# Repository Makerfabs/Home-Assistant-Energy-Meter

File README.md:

# Makerfabs Home Assistant Energy Meter

## Intruduce

[Product Link]()

[Wiki Link](https://wiki.makerfabs.com/How%20to%20use%20Energy%20Meter%20for%20Home%20Assistant.html)

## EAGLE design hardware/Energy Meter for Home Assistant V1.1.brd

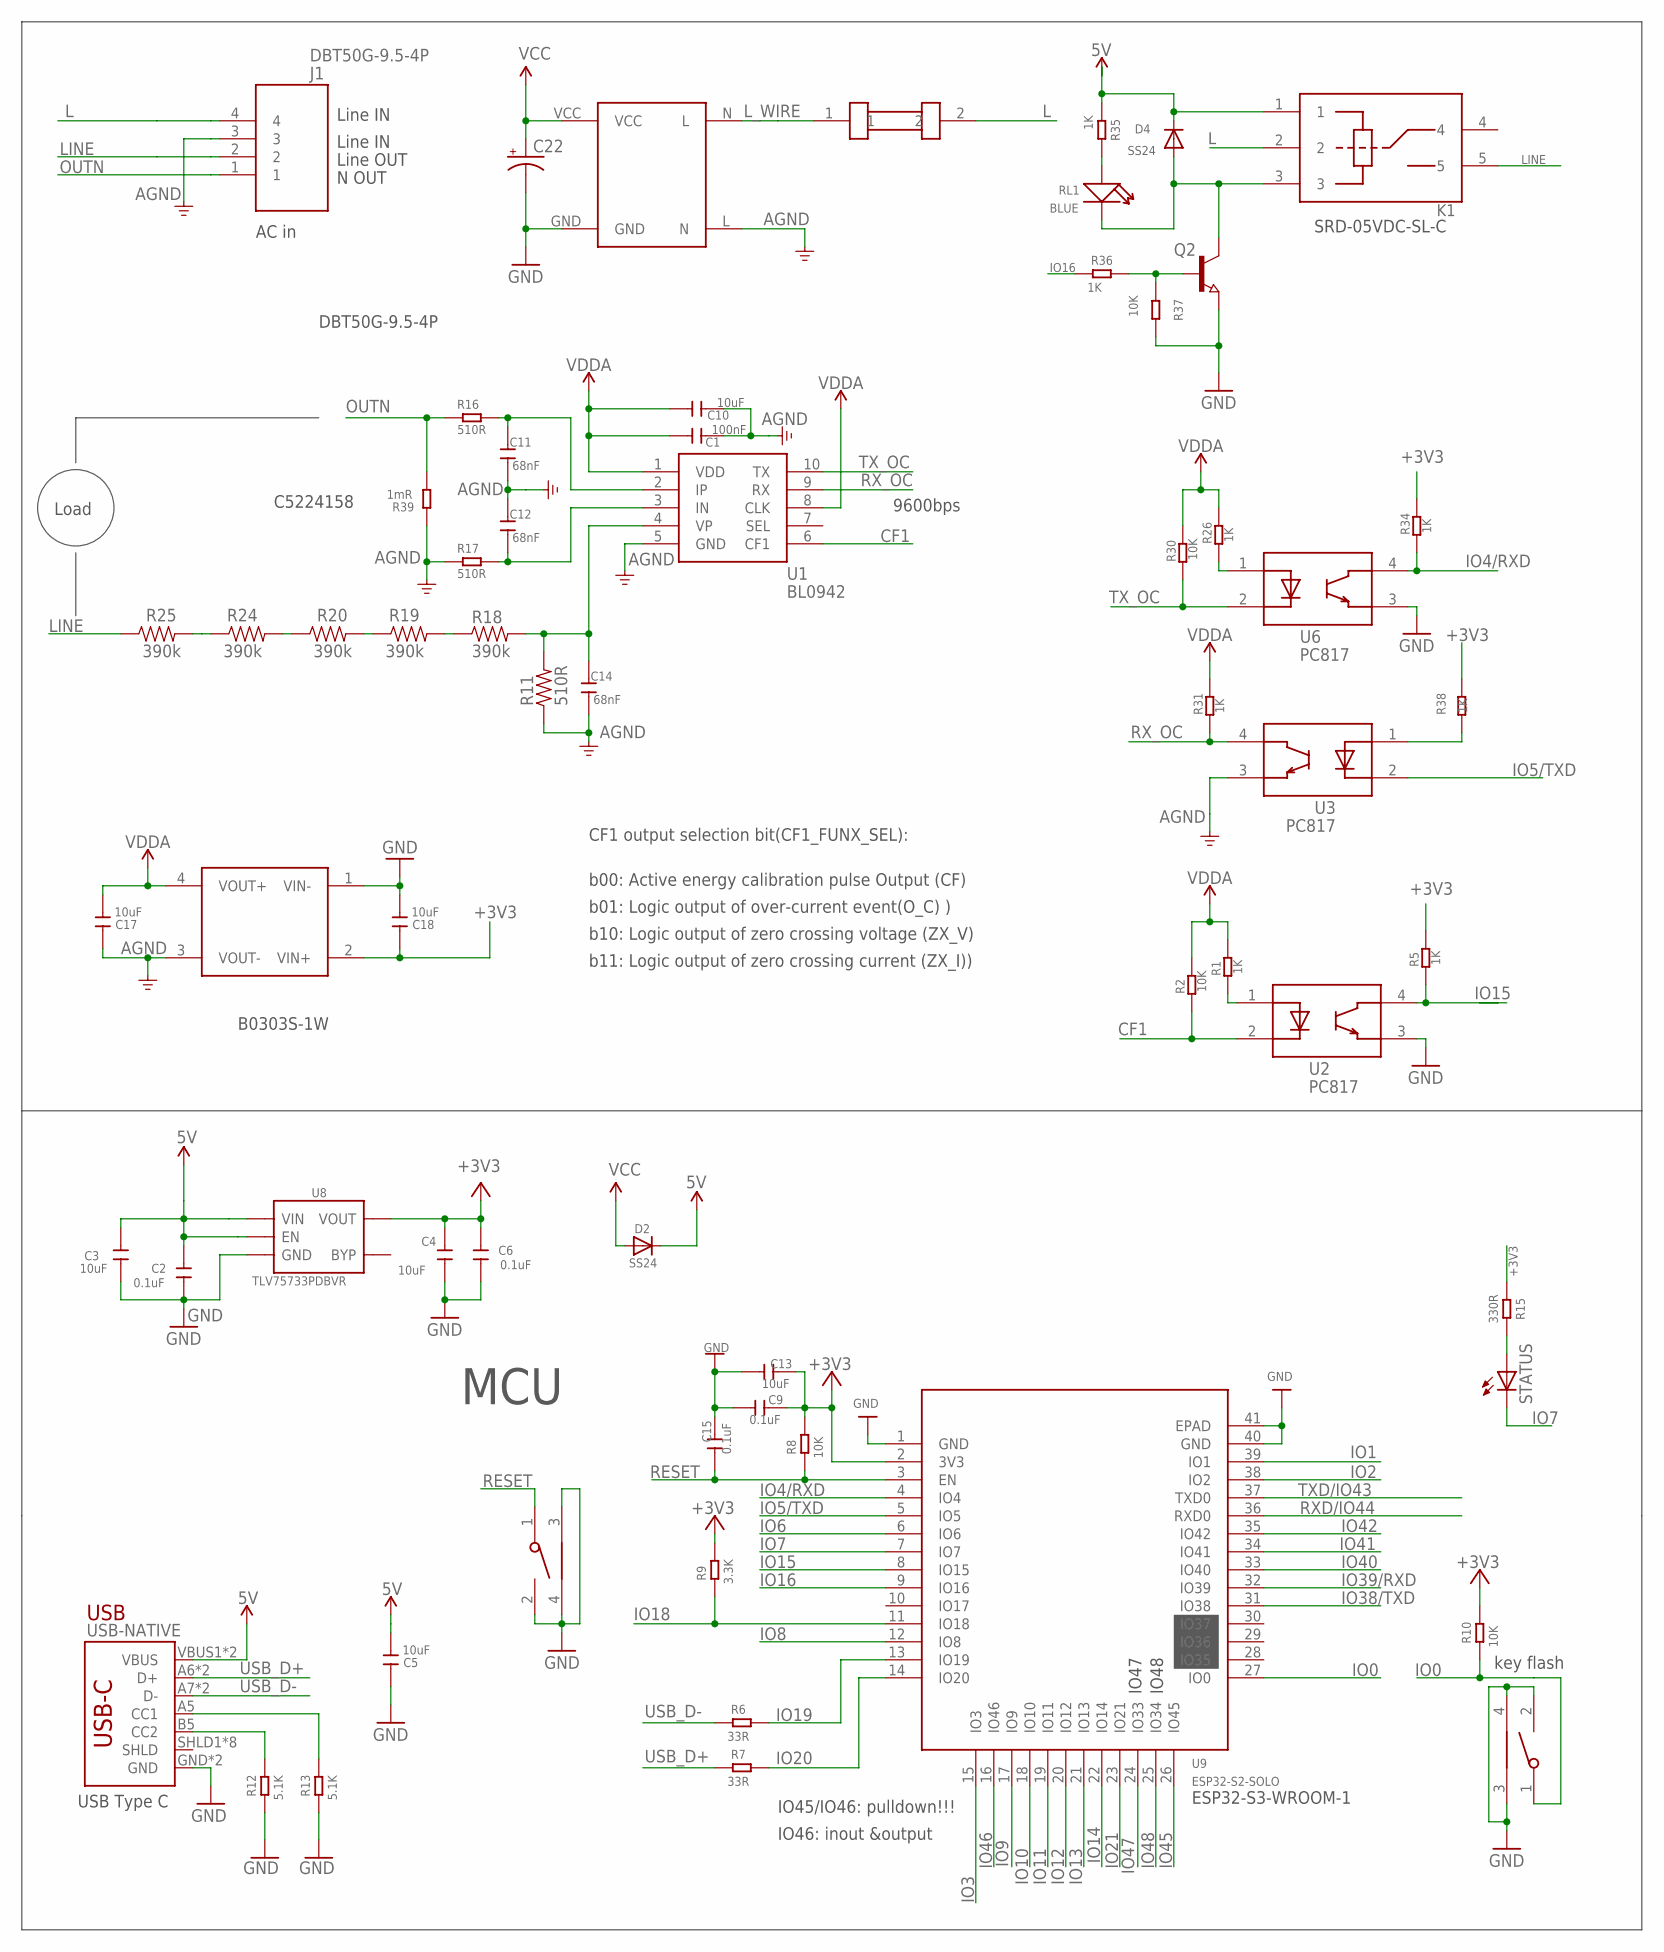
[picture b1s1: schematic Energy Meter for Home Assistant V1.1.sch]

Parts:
BOOT: TS24CA; 2*4*3.5MM
C1: 100nF; 0603
C2, C6, C9, C15: 0.1uF; 0603
C3, C4, C5, C10, C13, C17, C18: 10uF; 0603
C11, C12, C14: 68nF; 0603
C22: CAP_POL3528-KIT; EIA3528-KIT
D2, D4: SS24; SMADIODE
F1: FUSE01; FUSE01-D4XL11
J1: DBT50G-9.5-4P
K1: JQC3FF; DIP5_JQC3FF
Q2: NPN-TRANSISTOR_SOT23; SOT23
R1, R5, R26, R31, R34, R35, R36, R38: 1K; R0603
R2, R8, R10, R30, R37: 10K; R0603
R6, R7: 33R; R0603
R9: 3.3K; R0603
R11: 510R; 1206
R12, R13: 5.1K; R0603
R15: 330R; R0603
R16, R17: 510R; R0603
R18, R19, R20, R24, R25: 390k; 1206
R39: 1mR; DISCRETE_R2512
RL1: BLUE; LED-0603
RST: TS24CA; 2*4*3.5MM
STATUS: LED5MM
U1: BL0942; SOP8-100P-600L500W175H
U2, U3, U6: PC817; SMD4-254P-1016L460W
U5: AC-DCHLK01; HLK-PM01
U7: B0303S
U8: TLV75733PDBVR; SOT23-5
U9: ESP32­S2­SOLO; ESP32-­S2-­SOLO
USB-NATIVE: USB_C5; USB-C-16P-5

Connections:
5V: C2.2, C3.2, C5.1, D2.C, D4.C, K1.1, R35.1, U8.1 (VIN), U8.3 (EN), USB-NATIVE.VBUS1 (VBUS), USB-NATIVE.VBUS2 (VBUS)
+3V3: C4.2, C6.2, C9.2, C13.2, C18.2, R5.2, R8.2, R9.2, R10.2, R15.1, R34.2, R38.2, U7.2 (VIN+), U8.5 (VOUT), U9.2 (3V3)
AGND: C1.1, C10.1, C11.2, C12.1, C14.2, C17.2, J1.3, R11.1, R17.2, R39.1, U1.5 (GND), U3.3, U5.L (N), U7.3 (VOUT-)
CF1: R2.1, U1.6 (CF1), U2.2
GND: BOOT.2, BOOT.3, BOOT.4, C2.1, C3.1, C4.1, C5.2, C6.1, C9.1, C13.1, C15.2, C18.1, C22.C (-), Q2.2 (E), R12.1, R13.1, R37.2, RST.2, RST.3, RST.4, U2.3, U5.GND, U6.3, U7.1 (VIN-), U8.2 (GND), U9.1 (GND), U9.40 (GND), U9.41 (EPAD), USB-NATIVE.GND, USB-NATIVE.GND2 (GND)
IO0: BOOT.1, R10.1, U9.27 (IO0)
IO1: U9.39 (IO1)
IO2: U9.38 (IO2)
IO3: U9.15 (IO3)
IO4/RXD: R34.1, U6.4, U9.4 (IO4)
IO5/TXD: U3.2, U9.5 (IO5)
IO6: U9.6 (IO6)
IO7: STATUS.K (C), U9.7 (IO7)
IO8: U9.12 (IO8)
IO9: U9.17 (IO9)
IO10: U9.18 (IO10)
IO11: U9.19 (IO11)
IO12: U9.20 (IO12)
IO13: U9.21 (IO13)
IO14: U9.22 (IO14)
IO15: R5.1, U2.4, U9.8 (IO15)
IO16: R36.1, U9.9 (IO16)
IO18: R9.1, U9.11 (IO18)
IO19: R6.2, U9.13 (IO19)
IO20: R7.2, U9.14 (IO20)
IO21: U9.23 (IO21)
IO38/TXD: U9.31 (IO38)
IO39/RXD: U9.32 (IO39)
IO40: U9.33 (IO40)
IO41: U9.34 (IO41)
IO42: U9.35 (IO42)
IO45: U9.26 (IO45)
IO46: U9.16 (IO46)
IO47: U9.24 (IO33)
IO48: U9.25 (IO34)
L: F1.2, J1.4, K1.2
LINE: J1.2, K1.5, R25.1
L_WIRE: F1.1, U5.N (L)
unnamed: R1.1, U2.1
unnamed: R15.2, STATUS.A
unnamed: R13.2, USB-NATIVE.A5 (CC1)
unnamed: R38.1, U3.1
unnamed: C11.1, R16.1, U1.2 (IP)
unnamed: C12.2, R17.1, U1.3 (IN)
unnamed: R26.1, U6.1
unnamed: R12.2, USB-NATIVE.B5 (CC2)
unnamed: C14.1, R11.2, R18.2, U1.4 (VP)
unnamed: R20.1, R24.2
unnamed: R24.1, R25.2
unnamed: R35.2, RL1.+
unnamed: D4.A, K1.3, Q2.3 (C), RL1.-
unnamed: Q2.1 (B), R36.2, R37.1
unnamed: R19.1, R20.2
unnamed: R18.1, R19.2
OUTN: J1.1, R16.2, R39.2
RESET: C15.1, R8.1, RST.1, U9.3 (EN)
RXD/IO44: U9.36 (RXD0)
RX_OC: R31.1, U1.9 (RX), U3.4
TXD/IO43: U9.37 (TXD0)
TX_OC: R30.1, U1.10 (TX), U6.2
USB_D+: R7.1, USB-NATIVE.A6 (D+), USB-NATIVE.B6 (D+)
USB_D-: R6.1, USB-NATIVE.A7 (D-), USB-NATIVE.B7 (D-)
VCC: C22.A (+), D2.A, U5.VCC
VDDA: C1.2, C10.2, C17.1, R1.2, R2.2, R26.2, R30.2, R31.2, U1.1 (VDD), U1.8 (CLK), U7.4 (VOUT+)

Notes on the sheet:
AC in
SRD-05VDC-SL-C
C5224158
B0303S-1W
DBT50G-9.5-4P
Line IN
Line OUT
N OUT
Load
IO45/IO46: pulldown!!!
IO46: inout &output
USB
USB Type C
MCU
ESP32-S3-WROOM-1
IO47
IO48
key flash
9600bps
b00: Active energy calibration pulse Output (CF)
b01: Logic output of over-current event(O_C) )
b10: Logic output of zero crossing voltage (ZX_V)
b11: Logic output of zero crossing current (ZX_I))
CF1 output selection bit(CF1_FUNX_SEL):

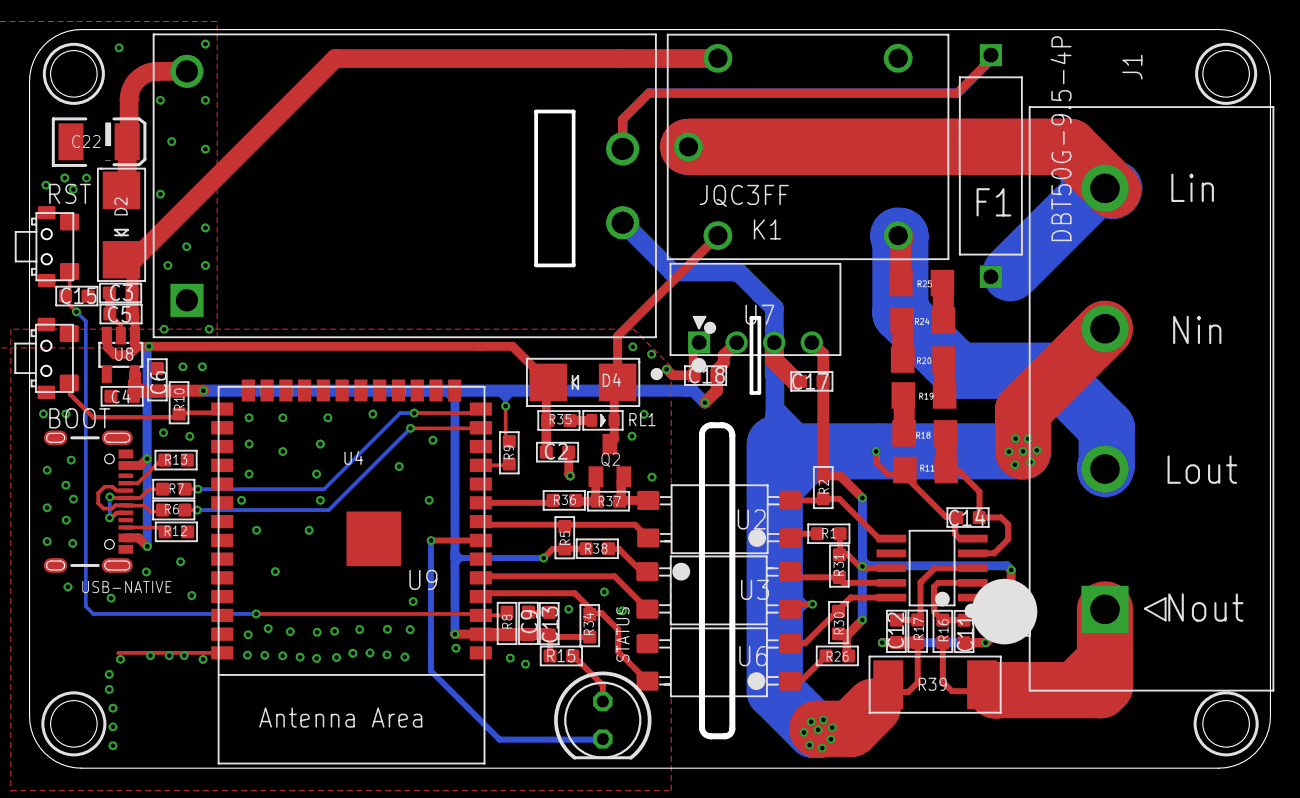
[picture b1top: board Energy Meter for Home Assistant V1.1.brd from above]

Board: 2 copper layers, 83.6 x 49.6 mm, 64 parts (1 on the bottom side), 41 nets.

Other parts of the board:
U$1: MAKERFABS_0.3

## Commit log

2026-01-03 add energy meter
2026-01-04 add datasheet
2026-01-15 update yaml
2026-01-15 fix yaml
2026-01-15 add custom components

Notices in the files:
parts and their libraries:
SparkFun-Resistors: Licensing: Creative Commons ShareAlike 4.0 International - https://creativecommons.org/licenses/by-sa/4.0
microbuilder: This work is placed in the public domain, and may be freely used for commercial and non-commercial work with the following conditions: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
